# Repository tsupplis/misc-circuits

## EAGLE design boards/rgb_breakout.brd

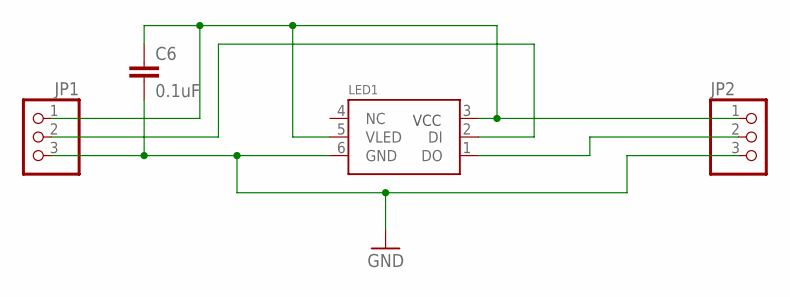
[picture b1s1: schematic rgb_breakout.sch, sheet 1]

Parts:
C6: 0.1uF; C0805
JP1, JP2: PINHD-1X3; 1X03
LED1: 5050WS2811W; RGBLED5050W

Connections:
GND: C6.2, JP1.3, JP2.3, LED1.6 (GND)
unnamed: JP2.2, LED1.1 (DO)
unnamed: JP1.2, LED1.2 (DI)
VCC: C6.1, JP1.1, JP2.1, LED1.3 (VCC), LED1.5 (VLED)

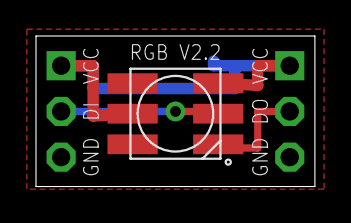
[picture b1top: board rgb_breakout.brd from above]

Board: 2 copper layers, 15.5 x 8.4 mm, 4 parts (1 on the bottom side), 4 nets.

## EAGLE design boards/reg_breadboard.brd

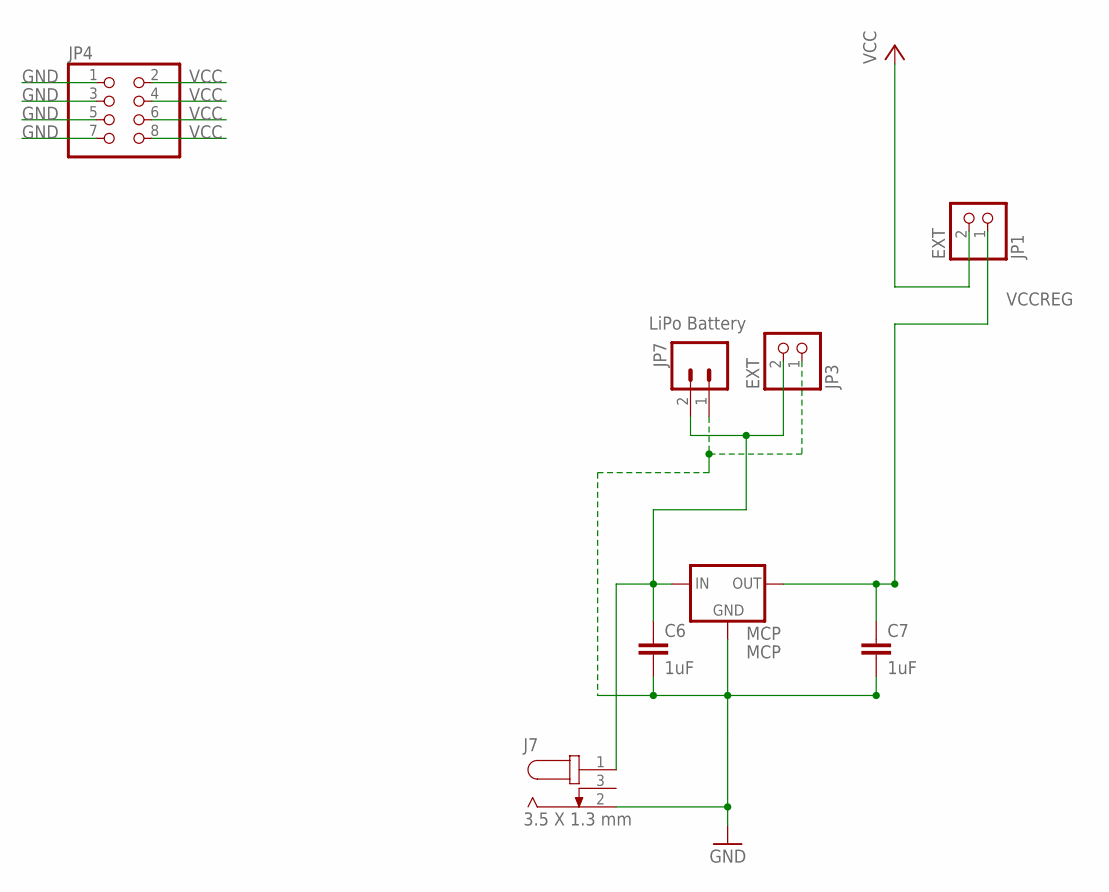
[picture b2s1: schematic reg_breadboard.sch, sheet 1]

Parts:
C6, C7: 1uF; C0805
J7: 3.5 X 1.3 mm; 3.5X1.3MM_DC_JACK
JP1, JP3: EXT; 1X02
JP4: PINHD-2X4; 2X04
JP7: LiPo Battery; JST-2-PTH
MCP: MCP; SOT-23

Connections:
GND: C6.2, C7.2, J7.2, JP3.1, JP4.1, JP4.3, JP4.5, JP4.7, JP7.1, MCP.1 (GND)
VCC: JP1.2, JP4.2, JP4.4, JP4.6, JP4.8
VCCEXT: C6.1, J7.1, JP3.2, JP7.2, MCP.3 (IN)
VCCREG: C7.1, JP1.1, MCP.2 (OUT)

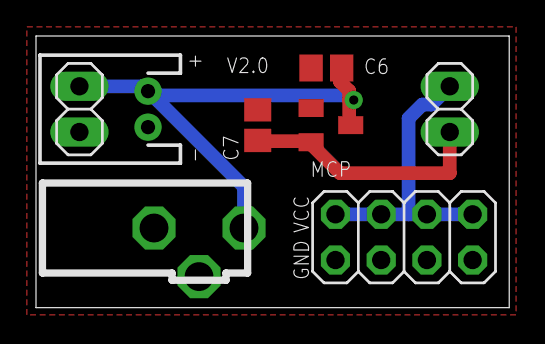
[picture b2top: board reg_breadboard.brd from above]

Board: 2 copper layers, 26.3 x 15.1 mm, 8 parts (0 on the bottom side), 4 nets.

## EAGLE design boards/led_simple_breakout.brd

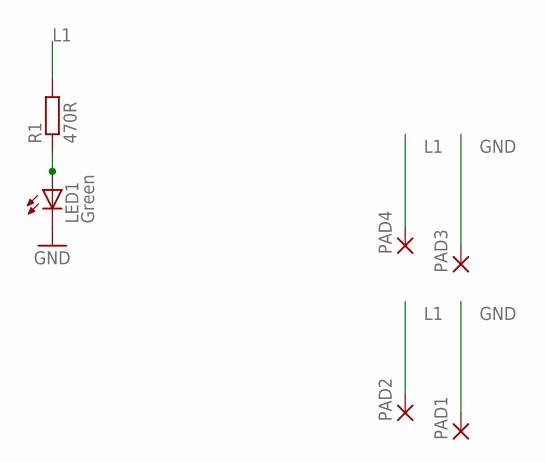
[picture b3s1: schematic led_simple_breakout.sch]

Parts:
LED1: Green; CHIPLED_1206
PAD1, PAD2, PAD3, PAD4: SMD2; SMD1,27-2,54
R1: 470R; R0805

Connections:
GND: LED1.C, PAD1.1, PAD3.1
L1: PAD2.1, PAD4.1, R1.2
unnamed: LED1.A, R1.1

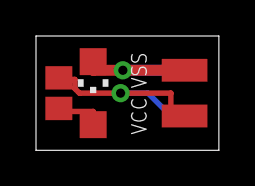
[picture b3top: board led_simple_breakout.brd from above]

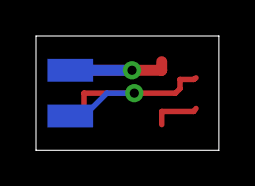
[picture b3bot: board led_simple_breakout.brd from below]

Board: 2 copper layers, 10.2 x 6.3 mm, 6 parts (2 on the bottom side), 3 nets.

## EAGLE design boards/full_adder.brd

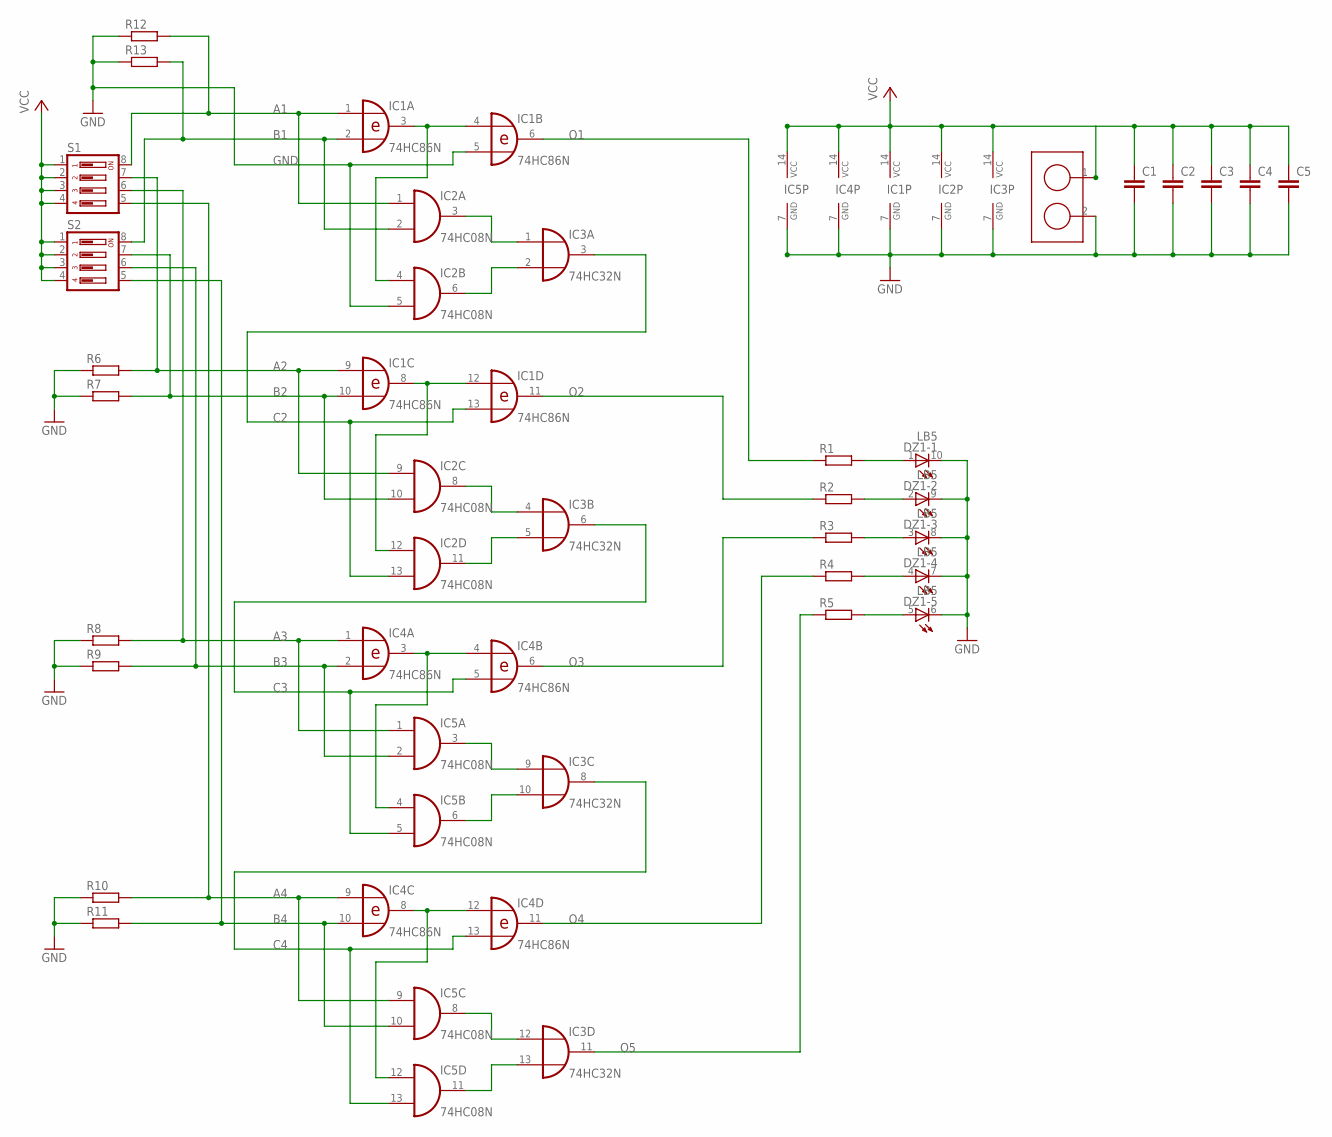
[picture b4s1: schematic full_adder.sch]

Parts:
C1, C2, C3, C4, C5: C-EU025-025X050; C025-025X050
DZ1: LB5
IC1, IC4: 74HC86N; DIL14
IC2, IC5: 74HC08N; DIL14
IC3: 74HC32N; DIL14
R1, R2, R3, R4, R5: R-EU_0204/7; 0204/7
R6, R7, R8, R9, R10, R11, R12, R13: 10K; 0204/7
S1, S2: DS04; DS-04
U$5: TB2

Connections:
A1: IC1.1 (I0), IC2.1 (I0), R12.2, S1.8
A2: IC1.9 (I0), IC2.9 (I0), R6.2, S1.7
A3: IC4.1 (I0), IC5.1 (I0), R8.2, S1.6
A4: IC4.9 (I0), IC5.9 (I0), R10.2, S1.5
B1: IC1.2 (I1), IC2.2 (I1), R13.2, S2.8
B2: IC1.10 (I1), IC2.10 (I1), R7.2, S2.7
B3: IC4.2 (I1), IC5.2 (I1), R9.2, S2.6
B4: IC4.10 (I1), IC5.10 (I1), R11.2, S2.5
C2: IC1.13 (I1), IC2.13 (I1), IC3.3 (O)
C3: IC3.6 (O), IC4.5 (I1), IC5.5 (I1)
C4: IC3.8 (O), IC4.13 (I1), IC5.13 (I1)
GND: C1.2, C2.2, C3.2, C4.2, C5.2, DZ1.6 (C), DZ1.7 (C), DZ1.8 (C), DZ1.9 (C), DZ1.10 (C), IC1.5 (I1), IC1.7 (GND), IC2.5 (I1), IC2.7 (GND), IC3.7 (GND), IC4.7 (GND), IC5.7 (GND), R6.1, R7.1, R8.1, R9.1, R10.1, R11.1, R12.1, R13.1, U$5.2
unnamed: IC1.8 (O), IC1.12 (I0), IC2.12 (I0)
unnamed: IC1.3 (O), IC1.4 (I0), IC2.4 (I0)
unnamed: IC4.8 (O), IC4.12 (I0), IC5.12 (I0)
unnamed: IC4.3 (O), IC4.4 (I0), IC5.4 (I0)
unnamed: IC2.3 (O), IC3.1 (I0)
unnamed: IC2.6 (O), IC3.2 (I1)
unnamed: IC3.9 (I0), IC5.3 (O)
unnamed: IC2.8 (O), IC3.4 (I0)
unnamed: IC2.11 (O), IC3.5 (I1)
unnamed: IC3.10 (I1), IC5.6 (O)
unnamed: DZ1.1 (A), R1.2
unnamed: IC3.12 (I0), IC5.8 (O)
unnamed: IC3.13 (I1), IC5.11 (O)
unnamed: DZ1.2 (A), R2.2
unnamed: DZ1.3 (A), R3.2
unnamed: DZ1.4 (A), R4.2
unnamed: DZ1.5 (A), R5.2
O1: IC1.6 (O), R1.1
O2: IC1.11 (O), R2.1
O3: IC4.6 (O), R3.1
O4: IC4.11 (O), R4.1
O5: IC3.11 (O), R5.1
VCC: C1.1, C2.1, C3.1, C4.1, C5.1, IC1.14 (VCC), IC2.14 (VCC), IC3.14 (VCC), IC4.14 (VCC), IC5.14 (VCC), S1.1, S1.2, S1.3, S1.4, S2.1, S2.2, S2.3, S2.4, U$5.1

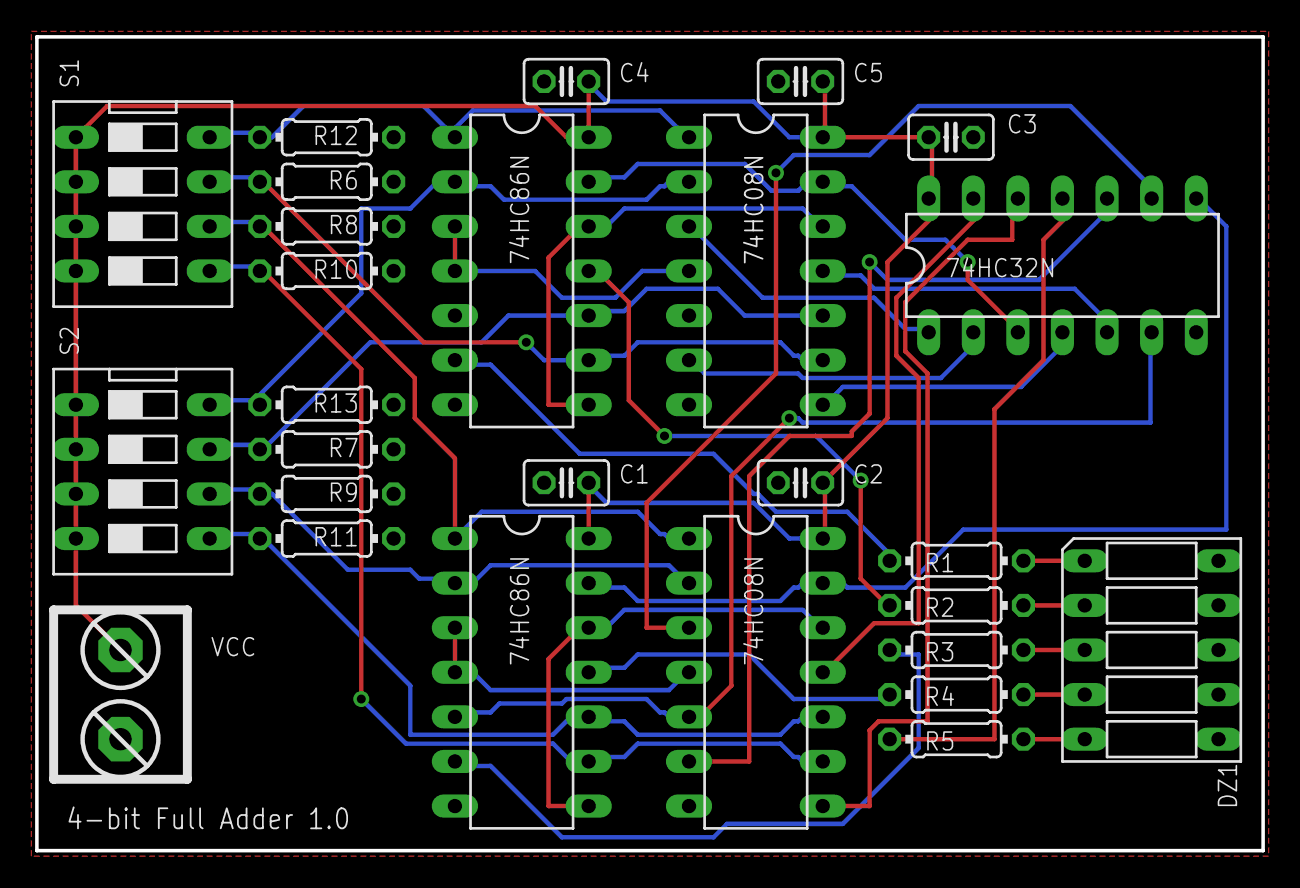
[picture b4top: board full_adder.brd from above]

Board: 2 copper layers, 69.9 x 46.4 mm, 27 parts (0 on the bottom side), 35 nets.

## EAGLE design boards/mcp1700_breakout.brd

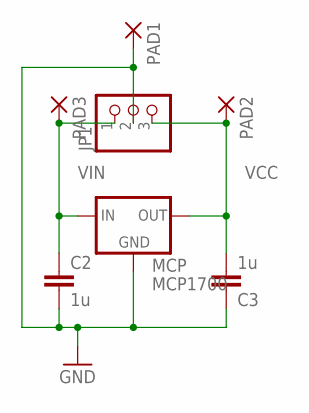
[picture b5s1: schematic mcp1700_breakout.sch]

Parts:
C2, C3: 1u; C0805
JP1: PINHD-1X3; 1X03
MCP: MCP1700; SOT-23
PAD1, PAD2, PAD3: SMD2; SMD1,27-2,54

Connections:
GND: C2.2, C3.1, JP1.2, MCP.1 (GND), PAD1.1
VCC: C3.2, JP1.3, MCP.2 (OUT), PAD2.1
VIN: C2.1, JP1.1, MCP.3 (IN), PAD3.1

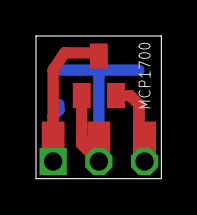
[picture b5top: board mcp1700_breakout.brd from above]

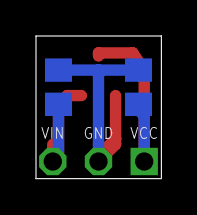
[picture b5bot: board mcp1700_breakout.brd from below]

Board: 2 copper layers, 7.0 x 7.9 mm, 7 parts (2 on the bottom side), 3 nets.

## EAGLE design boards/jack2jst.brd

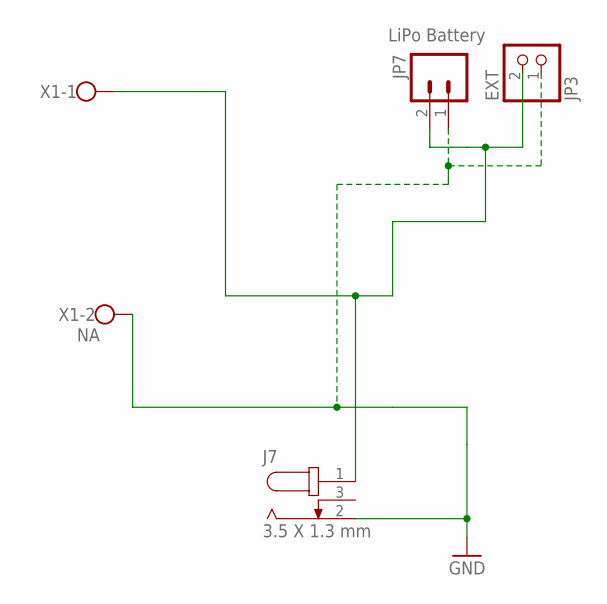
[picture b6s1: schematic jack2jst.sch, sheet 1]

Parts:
J7: 3.5 X 1.3 mm; 3.5X1.3MM_DC_JACK
JP3: EXT; 1X02
JP7: LiPo Battery; JST-2-PTH
X1: NA; W237-102

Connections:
GND: J7.2, JP3.1, JP7.1, X1.2
VCCEXT: J7.1, JP3.2, JP7.2, X1.1

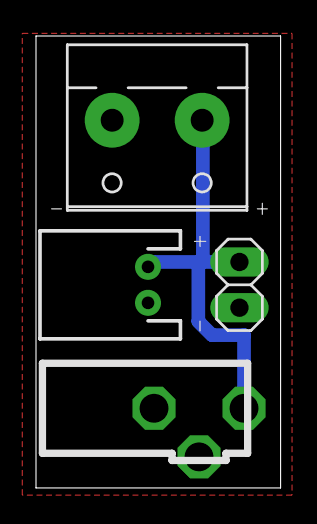
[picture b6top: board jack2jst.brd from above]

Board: 2 copper layers, 13.6 x 25.1 mm, 4 parts (0 on the bottom side), 2 nets.

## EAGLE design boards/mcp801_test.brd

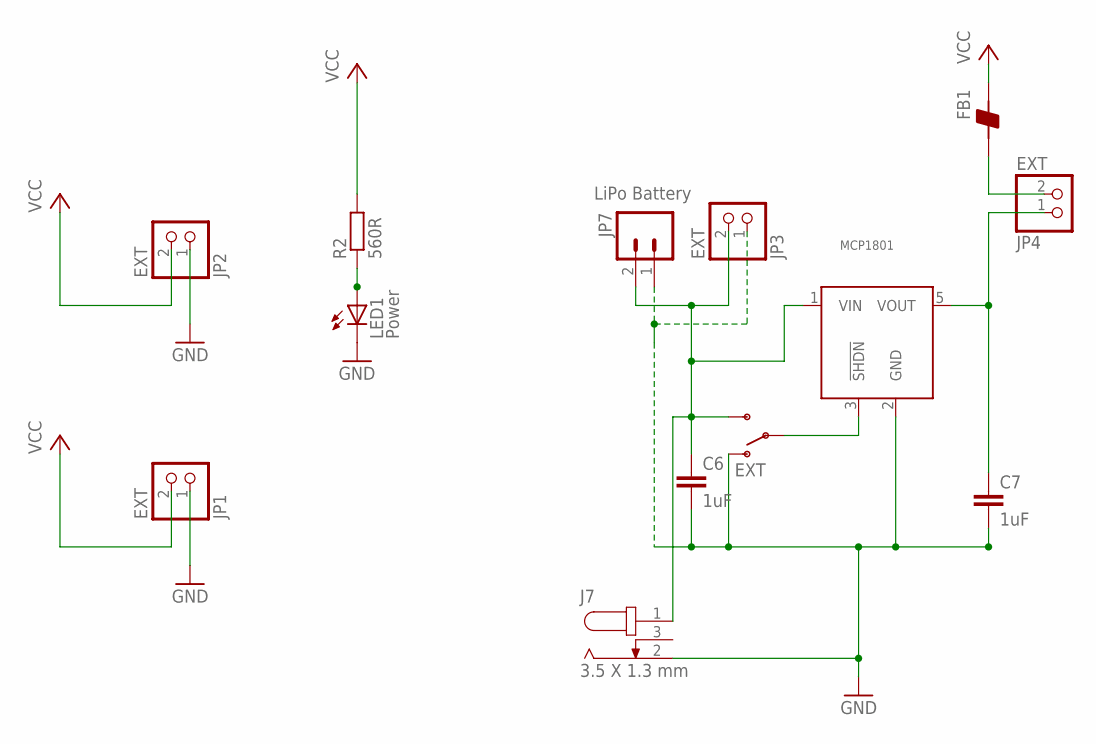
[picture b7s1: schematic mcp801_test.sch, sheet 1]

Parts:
C6, C7: 1uF; C0805
FB1: BEAD-0805; 0805
J7: 3.5 X 1.3 mm; 3.5X1.3MM_DC_JACK
JP1, JP2, JP3, JP4: EXT; 1X02
JP7: LiPo Battery; JST-2-PTH
LED1: Power; CHIPLED_1206
MCP1801: MCP180XSOT-23-5; SOT-23-5
ON: EXT; SWITCH-SPDT
R2: 560R; R0805

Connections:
GND: C6.2, C7.2, J7.2, JP1.1, JP2.1, JP3.1, JP7.1, LED1.C, MCP1801.2 (GND), ON.1 (O)
unnamed: MCP1801.3 (!SHDN), ON.2
unnamed: FB1.1, JP4.2
unnamed: LED1.A, R2.1
VCC: FB1.2, JP1.2, JP2.2, R2.2
VCCEXT: C6.1, J7.1, JP3.2, JP7.2, MCP1801.1 (VIN), ON.3 (S)
VCCREGOUT: C7.1, JP4.1, MCP1801.5 (VOUT)

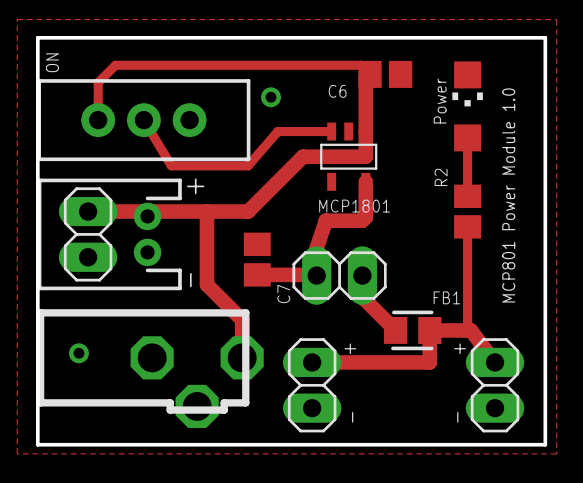
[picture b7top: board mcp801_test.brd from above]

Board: 2 copper layers, 28.2 x 22.6 mm, 13 parts (0 on the bottom side), 7 nets.

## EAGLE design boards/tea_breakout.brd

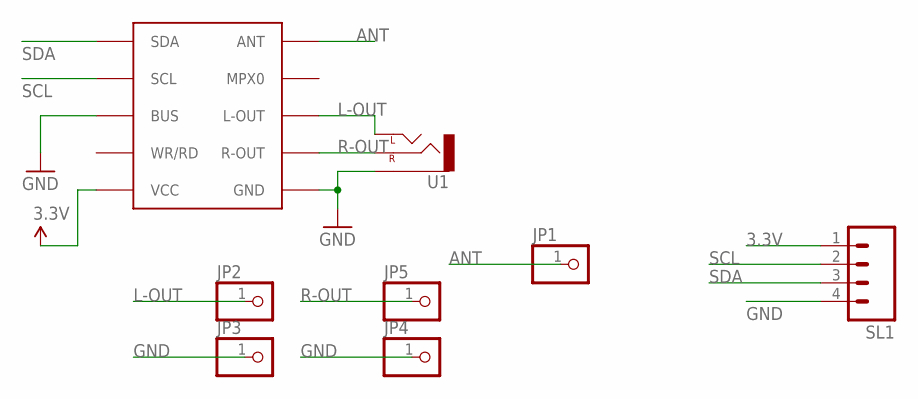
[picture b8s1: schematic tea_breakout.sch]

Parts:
JP1, JP2, JP3, JP4, JP5: PINHD-1X1; 1X01
SL1: M041X04_NO_SILK; 1X04_NO_SILK
U1: AUDIO-JACKPTH; AUDIO-JACK
U$1: PL102BC-N

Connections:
3.3V: SL1.1, U$1.PAD5 (VCC)
ANT: JP1.1, U$1.PAD11 (ANT)
GND: JP3.1, JP4.1, SL1.4, U1.SLEEVE, U$1.PAD3 (BUS), U$1.PAD6 (GND)
L-OUT: JP2.1, U1.TIP (LEFT), U$1.PAD9 (L-OUT)
R-OUT: JP5.1, U1.RING (RIGHT), U$1.PAD7 (R-OUT)
SCL: SL1.2, U$1.PAD2 (SCL)
SDA: SL1.3, U$1.PAD1 (SDA)

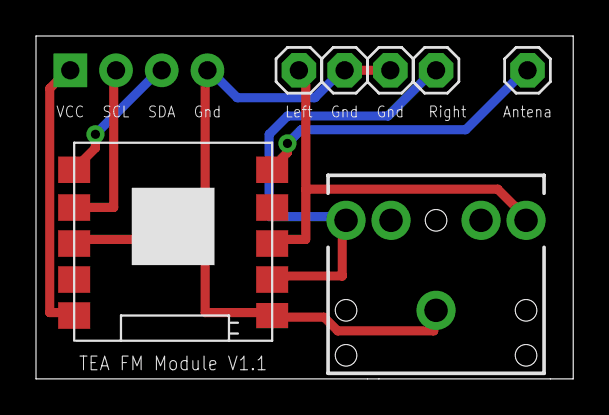
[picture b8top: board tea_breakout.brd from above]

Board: 2 copper layers, 29.8 x 19.0 mm, 8 parts (0 on the bottom side), 7 nets.

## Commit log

2016-04-05 Initial Content

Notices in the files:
parts and their libraries:
SparkFun: Licensing: CC v3.0 Share-Alike You are welcome to use this library for commercial purposes.
